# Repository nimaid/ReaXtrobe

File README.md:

An Open-Source Pitch-Reactive Addressable RGB LED Controller

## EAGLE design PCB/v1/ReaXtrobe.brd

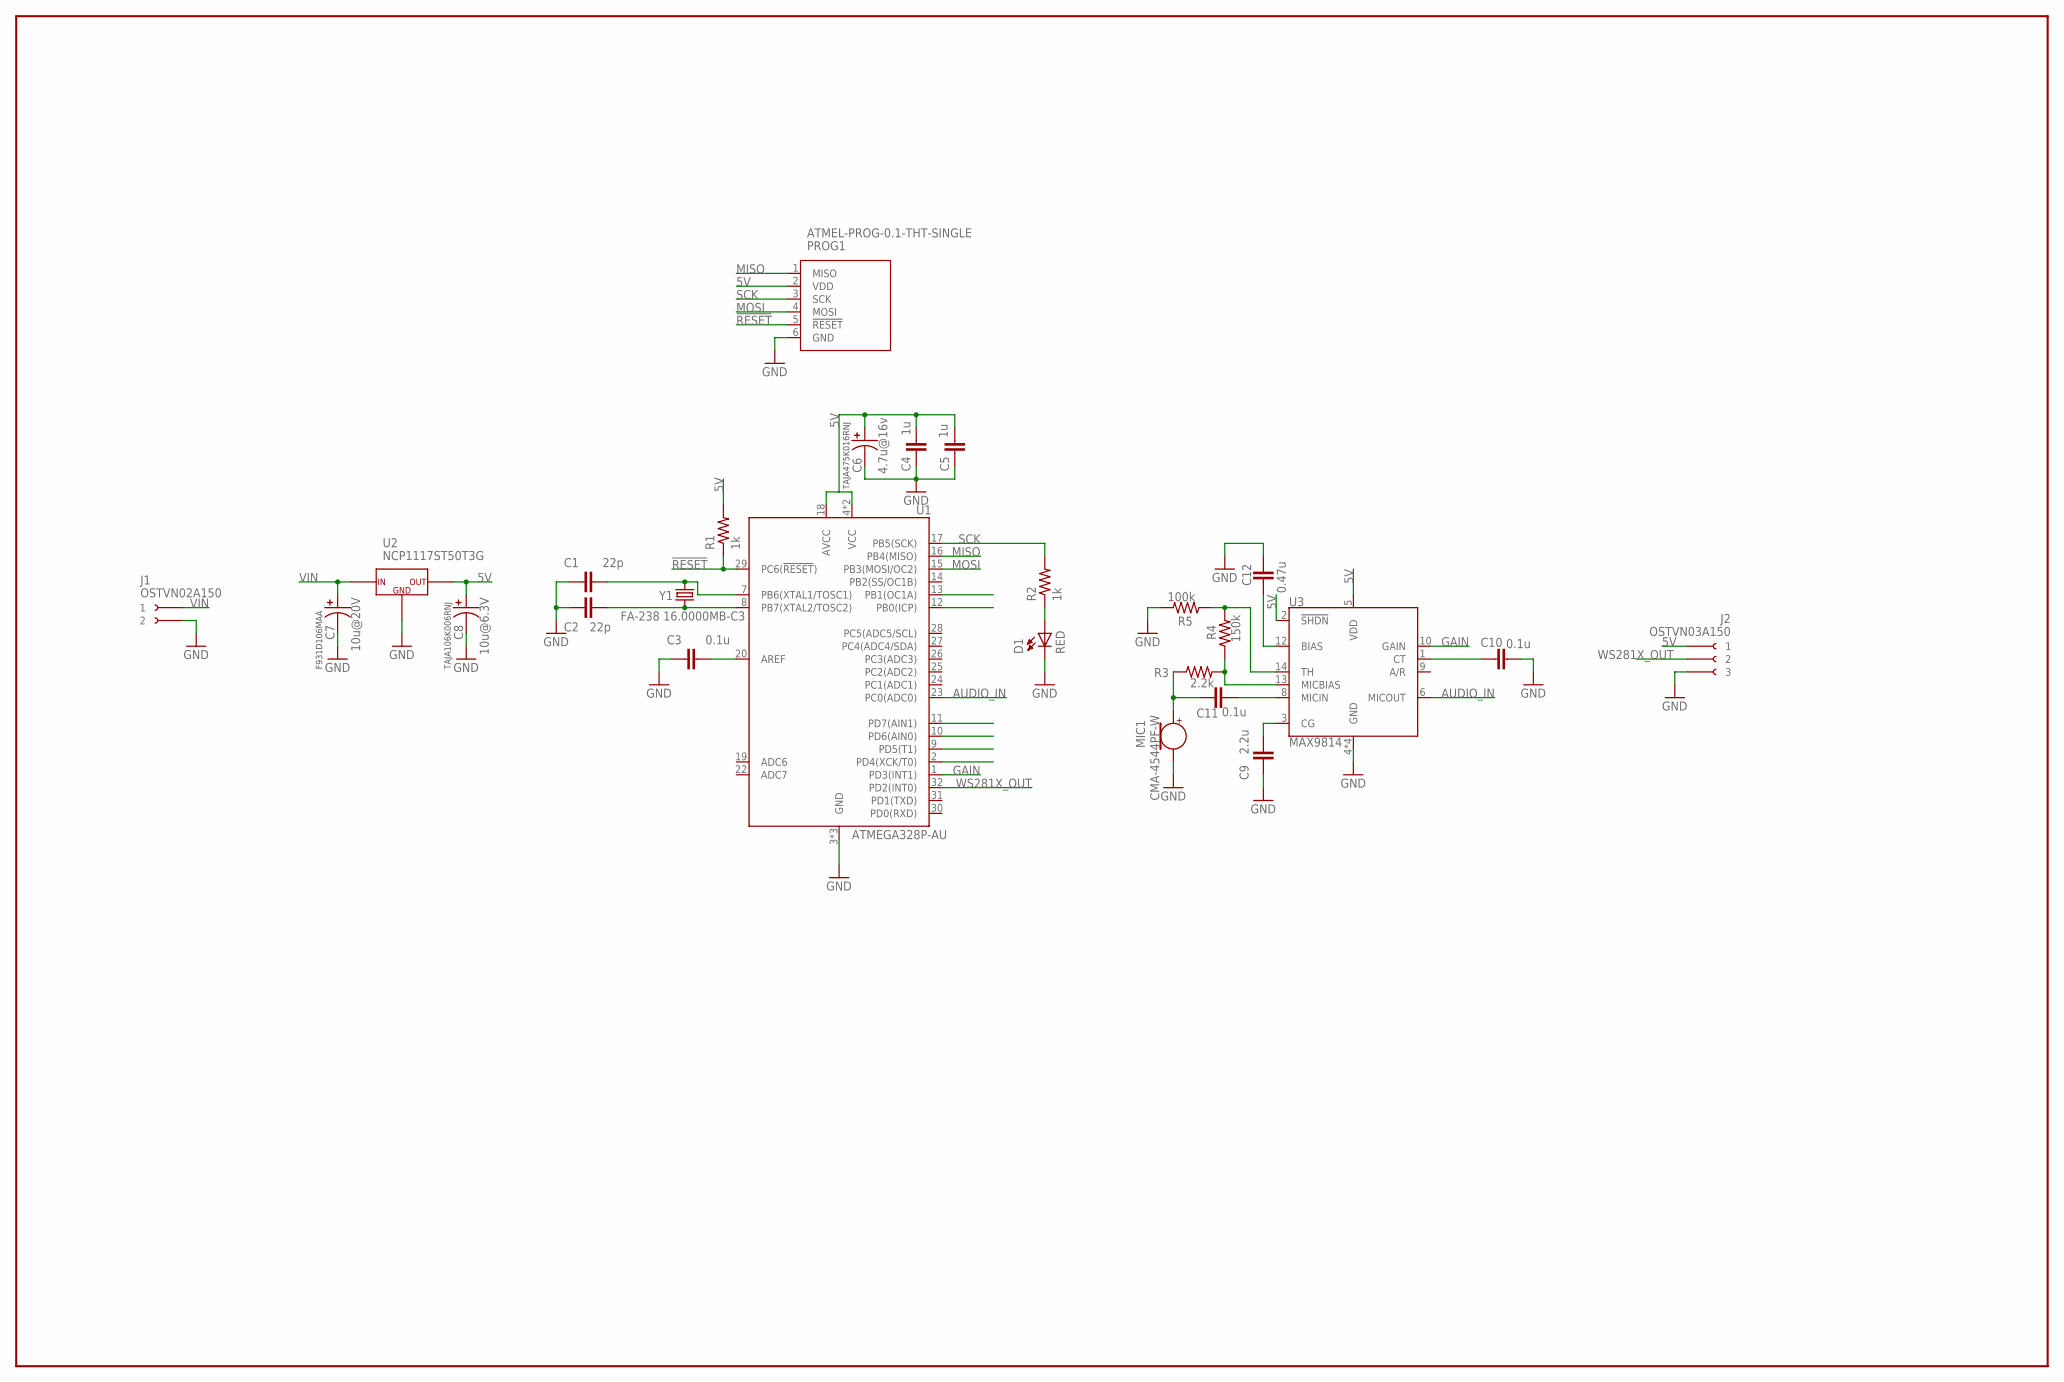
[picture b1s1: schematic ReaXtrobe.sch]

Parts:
C1, C2: 22p; C0603
C3, C10, C11: 0.1u; C0603
C4, C5: 1u; C0603
C6: 4.7u@16v; CAPMP3216X160
C7: 10u@20V; CAPMP3216X160
C8: 10u@6.3V; CAPMP3216X160
C9: 2.2u; C0603
C12: 0.47u; C0603
D1: RED; CHIP-LED0603
J1: OSTVN02A150
J2: OSTVN03A150
MIC1: CMA-4544PF-W; MIC_CMA-4544PF-W
PROG1: ATMEL-PROG-0.1-THT-SINGLE; HEADER-0.1-6
R1, R2: 1k; R0603
R3: 2.2k; R0603
R4: 150k; R0603
R5: 100k; R0603
U1: ATMEGA328P-AU; QFP80P900X900X120-32
U2: NCP1117ST50T3G; SOT223
U3: MAX9814; SON40P300X300X80-15T170X230
Y1: FA-238 16.0000MB-C3; OSCCC320X250X70

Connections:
5V: C4.2, C5.2, C6.A, C8.A, J2.P$1 (1), PROG1.2 (VDD), R1.2, U1.4 (VCC), U1.6 (VCC), U1.18 (AVCC), U2.2 (OUT), U3.2 (!SHDN), U3.5 (VDD)
!RESET: PROG1.5 (!RESET), R1.1, U1.29 (PC6(!RESET!))
AUDIO_IN: U1.23 (PC0(ADC0)), U3.6 (MICOUT)
GAIN: U1.1 (PD3(INT1)), U3.10 (GAIN)
GND: C1.1, C2.1, C3.1, C4.1, C5.1, C6.C, C7.C, C8.C, C9.1, C10.1, C12.1, D1.C (K), J1.P$2 (2), J2.P$3 (3), MIC1.2 (N), PROG1.6 (GND), R5.2, U1.3 (GND), U1.5 (GND), U1.21 (GND), U2.1 (GND), U3.4 (GND), U3.7 (GND), U3.11 (GND), U3.15 (GND)
MISO: PROG1.1 (MISO), U1.16 (PB4(MISO))
MOSI: PROG1.4 (MOSI), U1.15 (PB3(MOSI/OC2))
unnamed: C2.2, U1.8 (PB7(XTAL2/TOSC2)), Y1.1
unnamed: C1.2, U1.7 (PB6(XTAL1/TOSC1)), Y1.3 (2)
unnamed: C3.2, U1.20 (AREF)
unnamed: D1.A, R2.1
unnamed: C9.2, U3.3 (CG)
unnamed: C10.2, U3.1 (CT)
unnamed: C11.1, U3.8 (MICIN)
unnamed: C11.2, MIC1.1, R3.1
unnamed: R3.2, R4.1, U3.13 (MICBIAS)
unnamed: R4.2, R5.1, U3.14 (TH)
unnamed: C12.2, U3.12 (BIAS)
SCK: PROG1.3 (SCK), R2.2, U1.17 (PB5(SCK))
VIN: C7.A, J1.P$1 (1), U2.3 (IN)
WS281X_OUT: J2.P$2 (2), U1.32 (PD2(INT0))

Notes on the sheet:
TAJA475K016RNJ
F931D106MAA
TAJA106K006RNJ

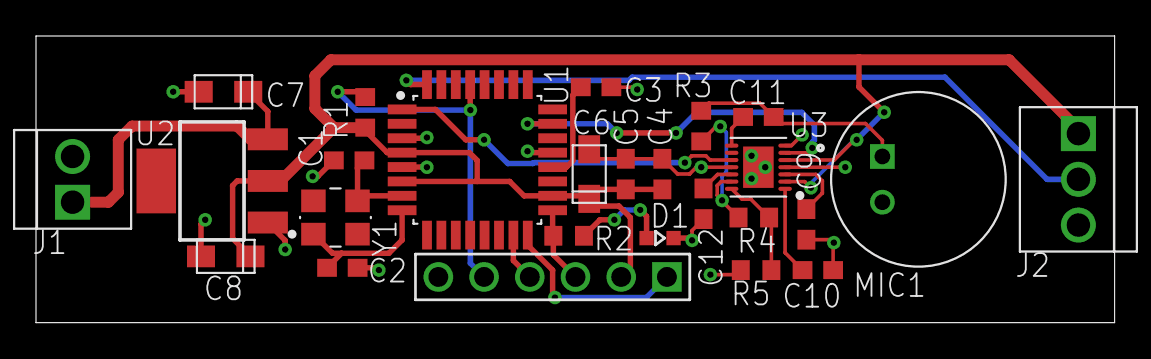
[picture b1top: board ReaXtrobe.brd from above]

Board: 2 copper layers, 59.9 x 15.9 mm, 26 parts (0 on the bottom side), 21 nets.

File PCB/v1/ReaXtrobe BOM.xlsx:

Qty | Reference Designators | Description | Manufacturer PN | Manufacturer | Supplier PN | Supplier | Notes | Sets | Qty In-House | Qty to Order
2 | C1, C2 | 22pF 6.3V 0603 SMD Ceramic Capacitor | CC0603JRNPO9BN220 | Yageo | 311-1062-1-ND | Digi-Key |  | 3 |  | 6 | https://www.digikey.com/short/p50t17
1 | C12 | 0.47uF 6.3V 0603 SMD Ceramic Capacitor | CL10B474KA8NFNC | Samsung Electro-Mechanics | 1276-2082-1-ND | Digi-Key |  |  |  | 3 | https://www.digikey.com/short/pdf0pw
3 | C3, C10, C11 | 0.1uF 6.3V 0603 SMD Ceramic Capacitor | CL10B104KB8NNNL | Samsung Electro-Mechanics | 1276-CL10B104KB8NNNLCT-ND | Digi-Key |  |  |  | 9
2 | C4, C5 | 1uF 6.3V 0603 SMD Ceramic Capacitor | CL10A105KP8NNNC | Samsung Electro-Mechanics | 1276-1182-1-ND | Digi-Key |  |  |  | 6
1 | C6 | 4.7uF 16V 1206 SMD Tantalum Capacitor | TAJA475K016RNJ | AVX Corporation | 478-3868-1-ND | Digi-Key |  |  |  | 3
1 | C7 | 10uF 20V 1206 SMD Tantalum Capacitor | F931D106MAA | AVX Corporation | 478-8275-1-ND | Digi-Key |  |  |  | 3
1 | C8 | 10uF 6.3V 1206 SMD Tantalum Capacitor | TAJA106K006RNJ | AVX Corporation | 478-1653-1-ND | Digi-Key |  |  |  | 3
1 | C9 | 2.2uF 6.3V 0603 SMD Ceramic Capacitor | CL10A225KQ8NNNC | Samsung Electro-Mechanics | 1276-1183-1-ND | Digi-Key |  |  |  | 3
1 | D1 | Red 0603 SMD LED | SML-D12U1WT86 | Rohm Semiconductor | SML-D12U1WT86CT-ND | Digi-Key |  |  |  | 3
1 | J1 | 0.1" 2x Screw Terminal | OSTVN02A150 | On Shore Technology Inc. | ED10561-ND | Digi-Key |  |  |  | 3
1 | J2 | 0.1" 3x Screw Terminal | OSTVN03A150 | On Shore Technology Inc. | ED10562-ND | Digi-Key |  |  |  | 3
1 | MIC1 | Electret THT Microphone | CMA-4544PF-W | CUI Inc. | 102-1721-ND | Digi-Key |  |  |  | 3
2 | R1, R2 | 1kΩ 0603 SMD Resistor | ESR03EZPJ102 | Rohm Semiconductor | RHM1.0KDCT-ND | Digi-Key |  |  |  | 6
1 | R3 | 2.2kΩ 0603 SMD Resistor | ERA-3AEB222V | Panasonic Electronic Components | P2.2KDBCT-ND | Digi-Key |  |  |  | 3
1 | R4 | 150kΩ 0603 SMD Resistor | CRGCQ0603F150K | TE Connectivity Passive Product | A129714CT-ND | Digi-Key |  |  |  | 3
1 | R5 | 100kΩ 0603 SMD Resistor | RR0816P-104-D | Susumu | RR08P100KDCT-ND | Digi-Key |  |  |  | 3
1 | U1 | Atmel 8-bit 32k SMD Microcontroller | ATMEGA328P-AU | Microchip Technology | ATMEGA328P-AURCT-ND | Digi-Key |  |  |  | 3
1 | U2 | 5V SMD Linear Voltage Regulator | NCP1117ST50T3G | ON Semiconductor | NCP1117ST50T3GOSCT-ND | Digi-Key |  |  |  | 3
1 | U3 | Electret Microphone Amplifier w/ AGC | MAX9814ETD+T | Maxim Integrated | MAX9814ETD+TCT-ND | Digi-Key |  |  |  | 3
1 | Y1 | 16MHz 18pF SMD Crystal | FA-238 16.0000MB-C3 | EPSON | SER3686CT-ND | Digi-Key |  |  |  | 3
0 |  |  |  |  |  |  |  |  |  | 0
0 |  |  |  |  |  |  |  |  |  | 0
0 |  |  |  |  |  |  |  |  |  | 0
0 |  |  |  |  |  |  |  |  |  | 0
0 |  |  |  |  |  |  |  |  |  | 0
0 |  |  |  |  |  |  |  |  |  | 0
0 |  |  |  |  |  |  |  |  |  | 0
0 |  |  |  |  |  |  |  |  |  | 0
0 |  |  |  |  |  |  |  |  |  | 0
0 |  |  |  |  |  |  |  |  |  | 0
0 |  |  |  |  |  |  |  |  |  | 0
0 |  |  |  |  |  |  |  |  |  | 0
0 |  |  |  |  |  |  |  |  |  | 0
0 |  |  |  |  |  |  |  |  |  | 0

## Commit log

2019-08-11 Inital file sync
2019-08-11 Create LICENSE
2019-08-11 PDF schematic
2019-08-11 Add BOM
2019-08-12 PCB mods, added first untested case.
2019-08-18 Rename, Gerbers
2019-08-18 Added logo
2019-08-18 Added new logo to board.
2019-08-21 V1 BOM
2019-08-21 Snap case v1
2019-11-18 Update BOM
